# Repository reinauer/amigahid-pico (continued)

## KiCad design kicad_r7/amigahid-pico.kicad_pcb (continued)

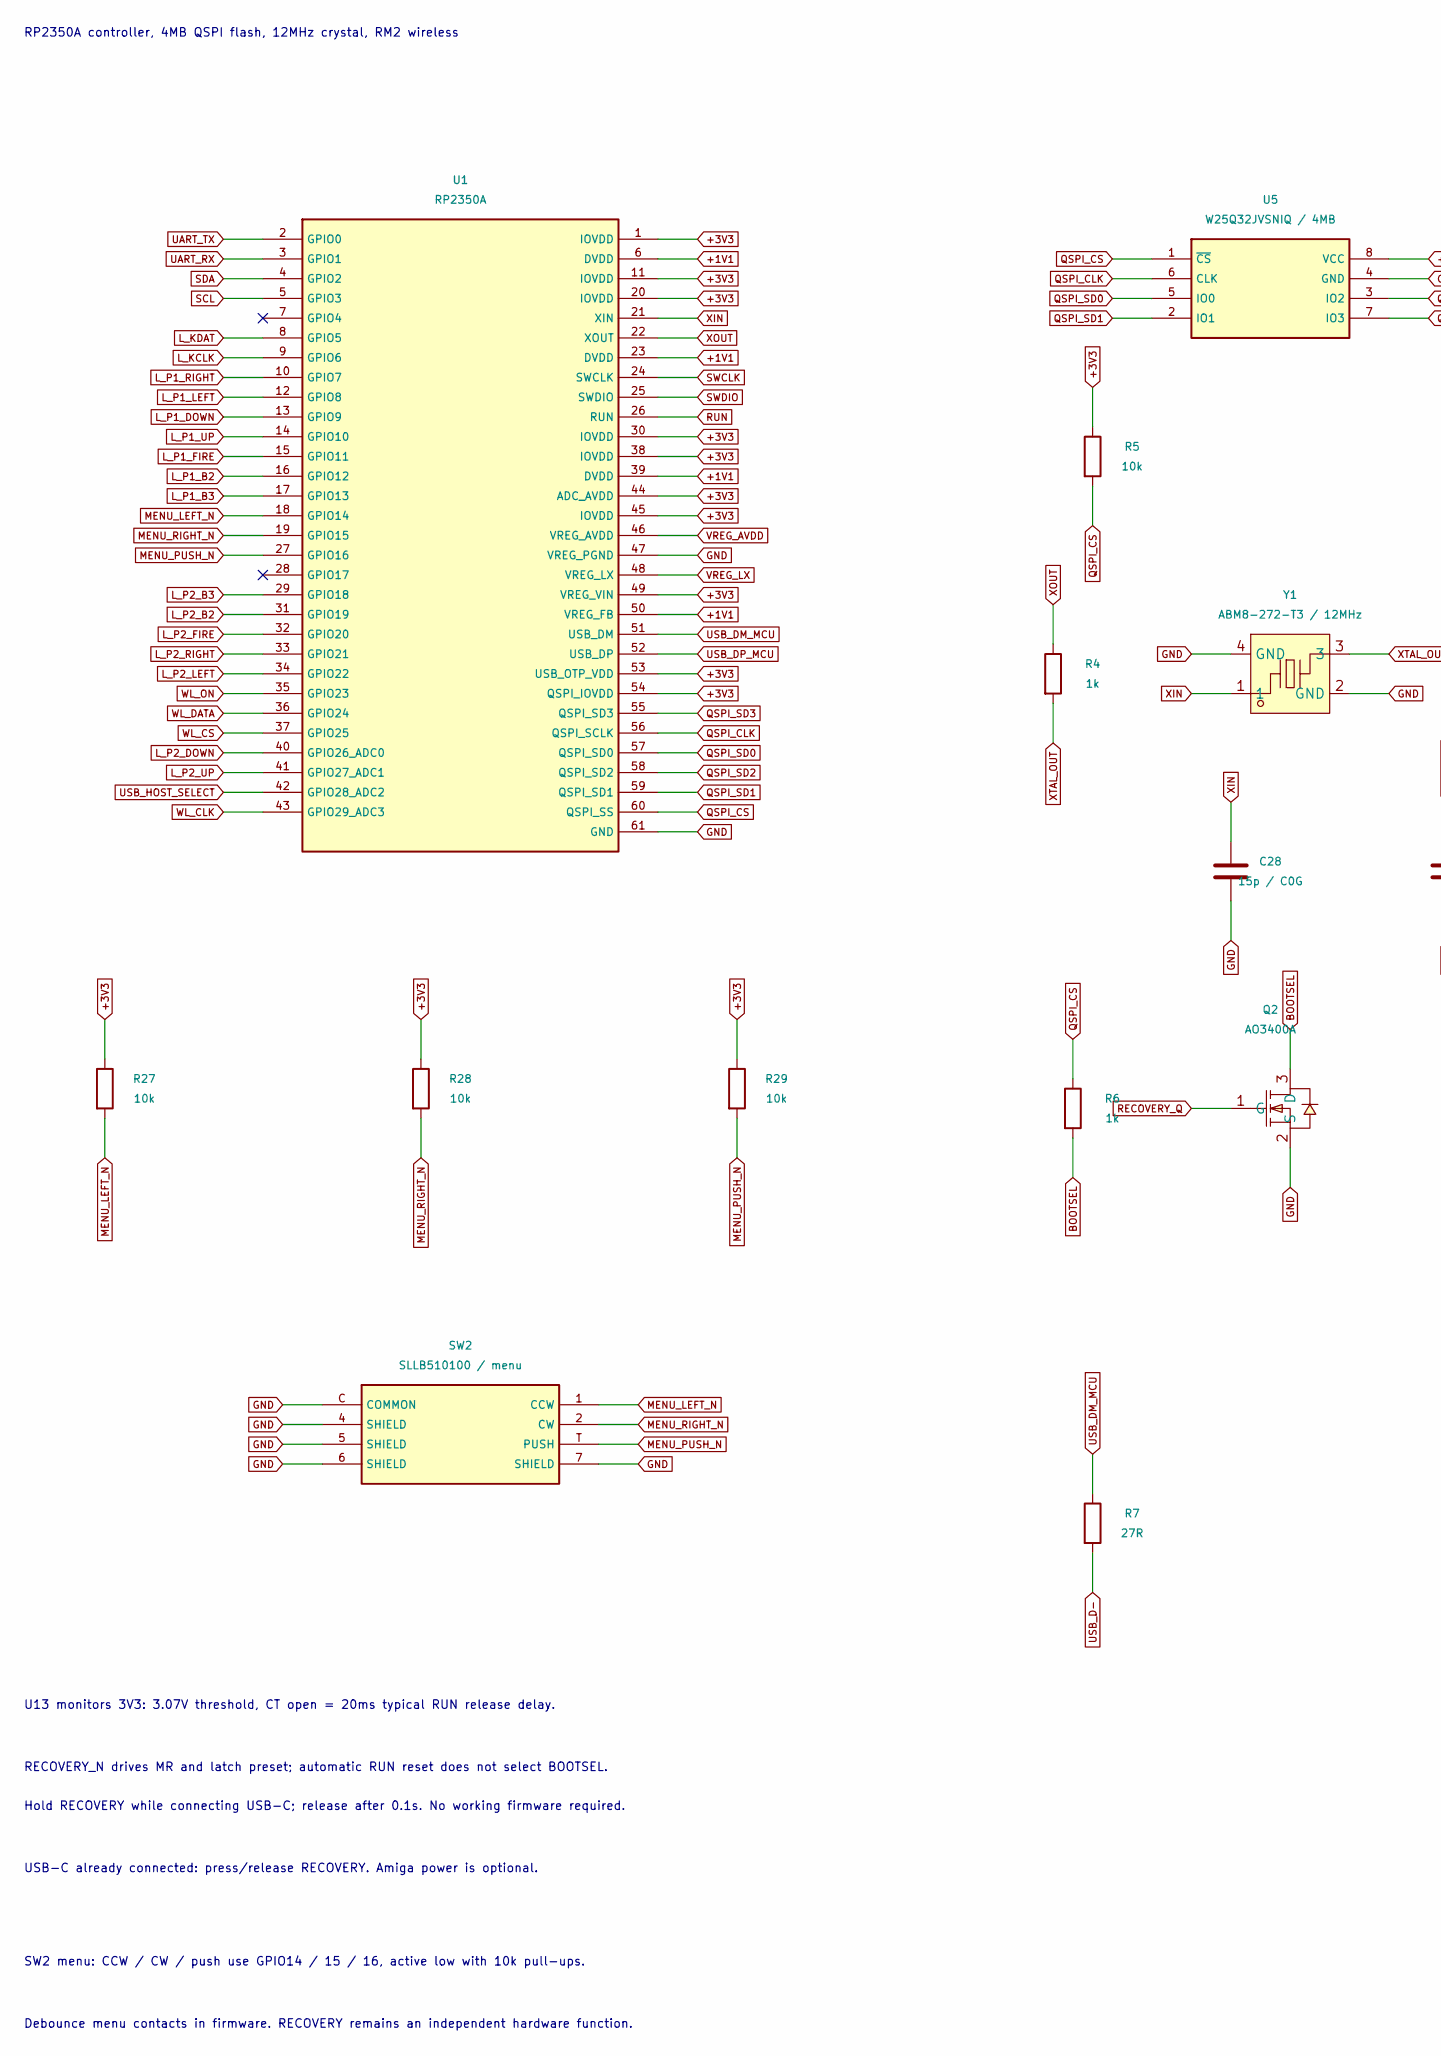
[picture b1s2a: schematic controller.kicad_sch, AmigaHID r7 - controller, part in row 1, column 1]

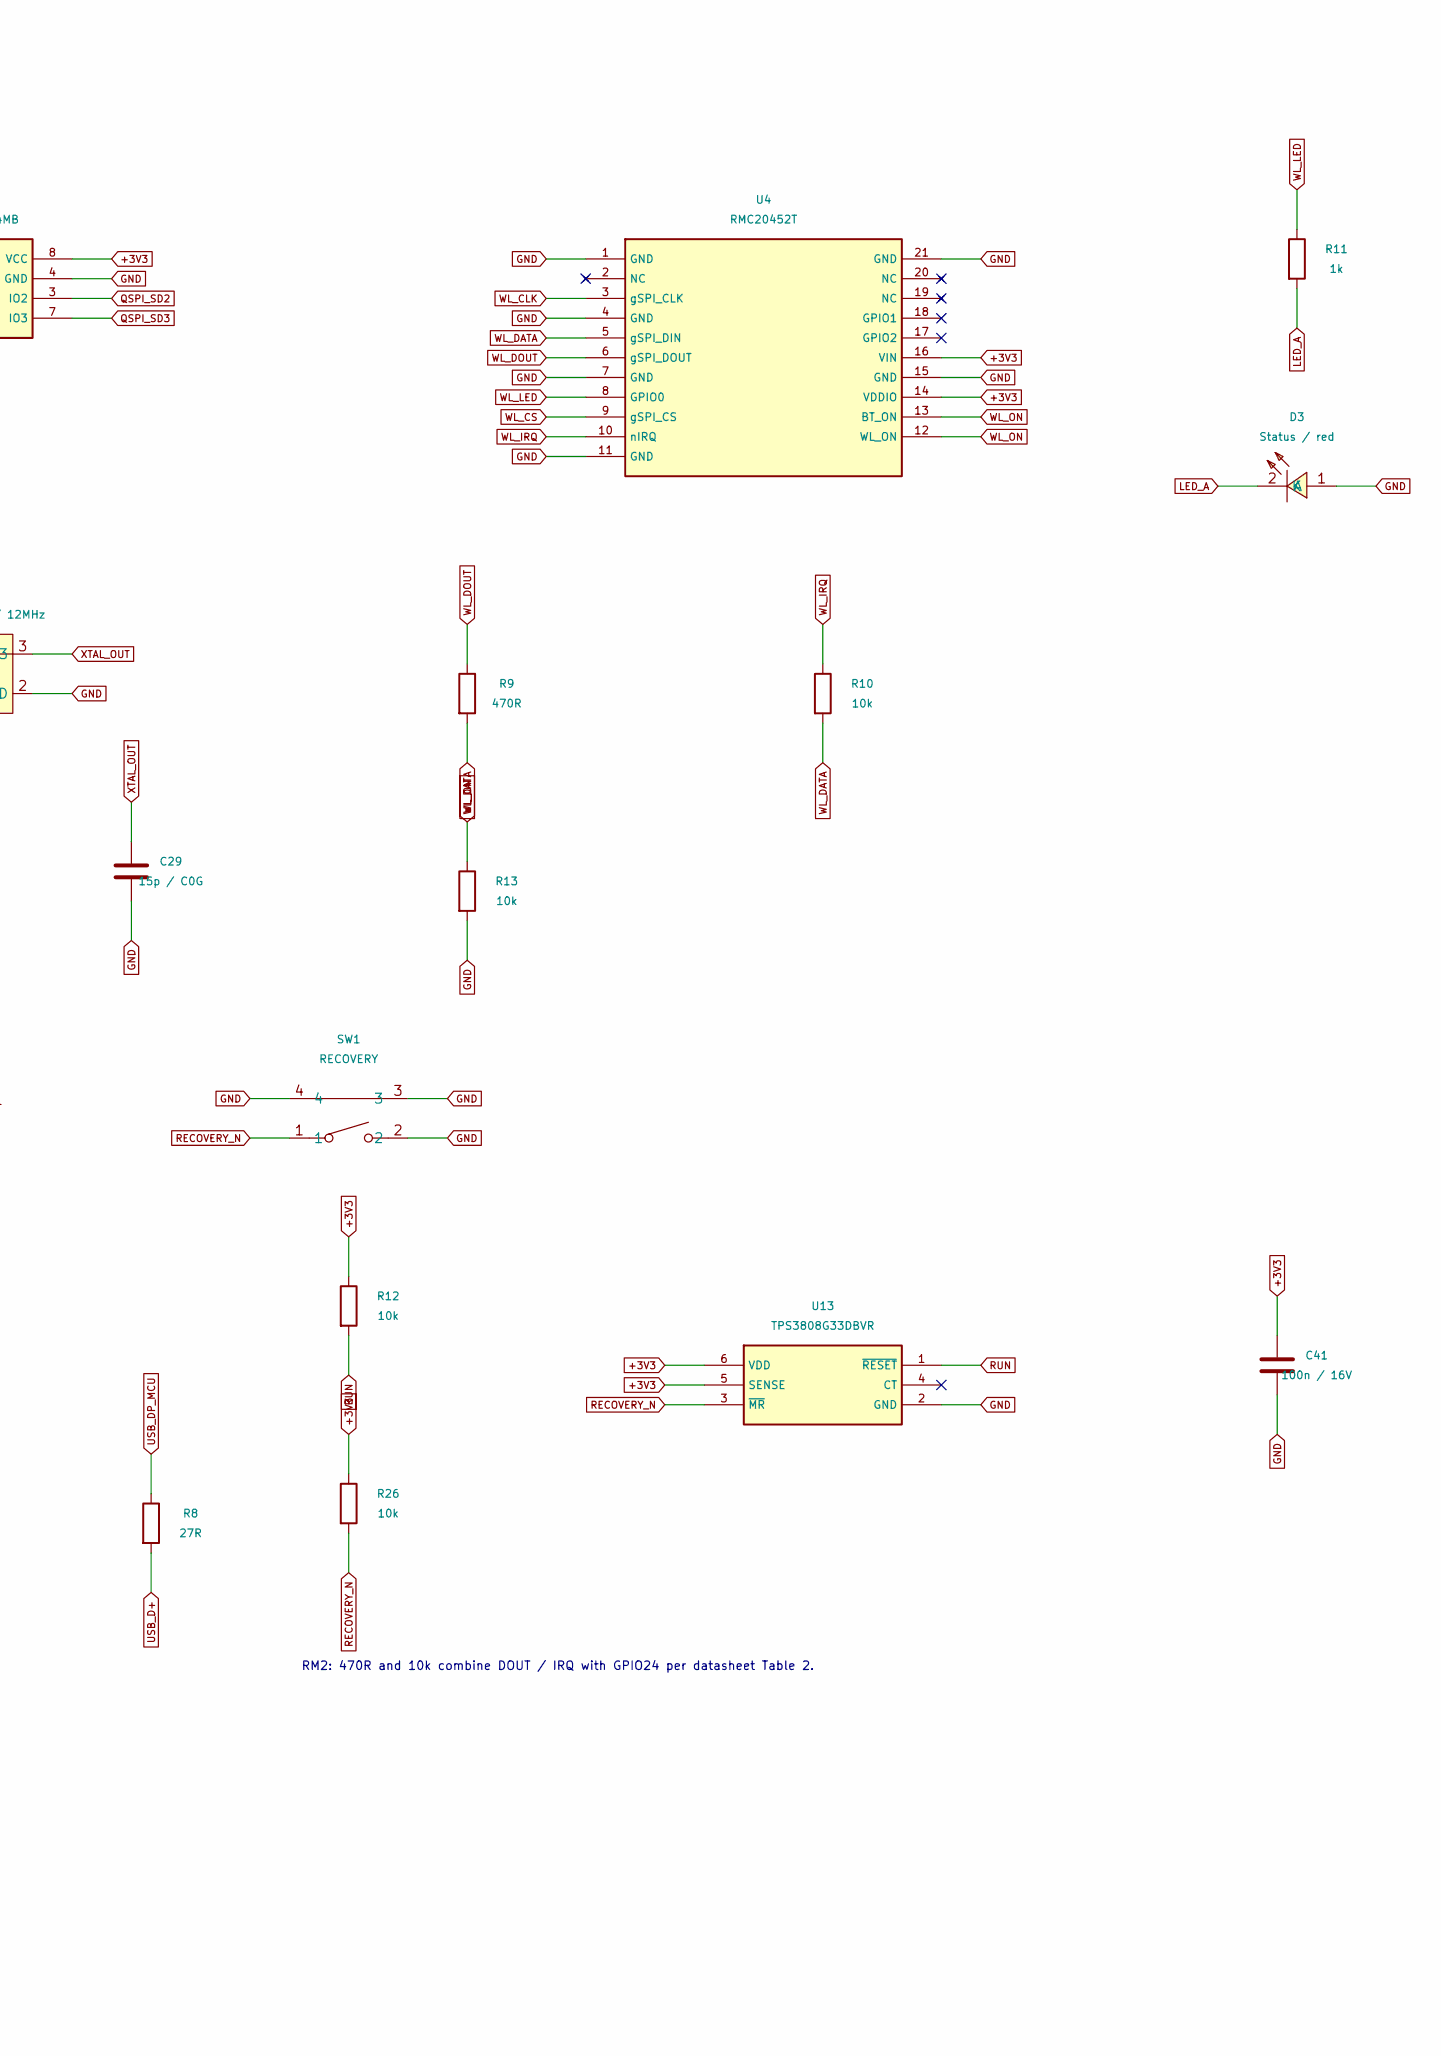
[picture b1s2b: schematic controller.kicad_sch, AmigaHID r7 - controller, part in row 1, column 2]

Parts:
C28, C29: 15p / C0G; C0402; MPN CL05C150JB5NNNC; LCSC Part # C86285
C41: 100n / 16V; C0402; MPN CL05B104KO5NNNC; LCSC Part # C1525
D3: Status / red; LED-SMD_L1.6-W0.8-R-RD; MPN KT-0603R; LCSC Part # C2286
Q2: AO3400A; SOT-23-3_L2.9-W1.3-P1.90-LS2.4-BR; MPN AO3400A; LCSC Part # C20917
R4, R6, R11: 1k; R0402; MPN 0402WGF1001TCE; LCSC Part # C11702
R5, R10, R12, R13, R26, R27, R28, R29: 10k; R0402; MPN 0402WGF1002TCE; LCSC Part # C25744
R7, R8: 27R; R0402; MPN 0402WGF270JTCE; LCSC Part # C25100
R9: 470R; R0402; MPN 0402WGF4700TCE; LCSC Part # C25117
SW1: RECOVERY; SW-SMD_2P-TS24CA; MPN TS24CA; LCSC Part # C393942
SW2: SLLB510100 / menu; SLLB510100; MPN SLLB510100; LCSC Part # C125039
U1: RP2350A; QFN-60_L7.0-W7.0-P0.40-TL-EP3.4; MPN RP2350A; LCSC Part # C42411118
U4: RMC20452T; WIRELM-SMD_RMC20452T; MPN RMC20452T; LCSC Part # C49451547
U5: W25Q32JVSNIQ / 4MB; SOP-8_L4.9-W3.9-P1.27-LS6.0-BL; MPN W25Q32JVSNIQ; LCSC Part # C5355146
U13: TPS3808G33DBVR; SOT-23-6; MPN TPS3808G33DBVR; LCSC Part # C43698
Y1: ABM8-272-T3 / 12MHz; CRYSTAL-SMD_4P-L3.2-W2.5-BL; MPN ABM8-272-T3; LCSC Part # C20625731

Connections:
+1V1: U1.6 (DVDD), U1.23 (DVDD), U1.39 (DVDD), U1.50 (VREG_FB); also elsewhere on the board
+3V3: C41.1, R5.1, R12.1, R26.1, R27.1, R28.1, R29.1, U1.1 (IOVDD), U1.11 (IOVDD), U1.20 (IOVDD), U1.30 (IOVDD), U1.38 (IOVDD), U1.44 (ADC_AVDD), U1.45 (IOVDD), U1.49 (VREG_VIN), U1.53 (USB_OTP_VDD), U1.54 (QSPI_IOVDD), U4.14 (VDDIO), U4.16 (VIN), U5.8 (VCC), U13.5 (SENSE), U13.6 (VDD); also elsewhere on the board
BOOTSEL: Q2.3 (D), R6.2
GND: C28.2, C29.2, C41.2, D3.1 (A), Q2.2 (S), R13.2, SW1.2, SW1.3, SW1.4, SW2.4 (SHIELD), SW2.5 (SHIELD), SW2.6 (SHIELD), SW2.7 (SHIELD), SW2.C (COMMON), U1.47 (VREG_PGND), U1.61 (GND), U4.1 (GND), U4.4 (GND), U4.7 (GND), U4.11 (GND), U4.15 (GND), U4.21 (GND), U5.4 (GND), U13.2 (GND), Y1.2 (GND), Y1.4 (GND); also elsewhere on the board
LED_A: D3.2 (K), R11.2
L_KCLK: U1.9 (GPIO6); also elsewhere on the board
L_KDAT: U1.8 (GPIO5); also elsewhere on the board
L_P1_B2: U1.16 (GPIO12); also elsewhere on the board
L_P1_B3: U1.17 (GPIO13); also elsewhere on the board
L_P1_DOWN: U1.13 (GPIO9); also elsewhere on the board
L_P1_FIRE: U1.15 (GPIO11); also elsewhere on the board
L_P1_LEFT: U1.12 (GPIO8); also elsewhere on the board
L_P1_RIGHT: U1.10 (GPIO7); also elsewhere on the board
L_P1_UP: U1.14 (GPIO10); also elsewhere on the board
L_P2_B2: U1.31 (GPIO19); also elsewhere on the board
L_P2_B3: U1.29 (GPIO18); also elsewhere on the board
L_P2_DOWN: U1.40 (GPIO26_ADC0); also elsewhere on the board
L_P2_FIRE: U1.32 (GPIO20); also elsewhere on the board
L_P2_LEFT: U1.34 (GPIO22); also elsewhere on the board
L_P2_RIGHT: U1.33 (GPIO21); also elsewhere on the board
L_P2_UP: U1.41 (GPIO27_ADC1); also elsewhere on the board
MENU_LEFT_N: R27.2, SW2.1 (CCW), U1.18 (GPIO14)
MENU_PUSH_N: R29.2, SW2.T (PUSH), U1.27 (GPIO16)
MENU_RIGHT_N: R28.2, SW2.2 (CW), U1.19 (GPIO15)
QSPI_CLK: U1.56 (QSPI_SCLK), U5.6 (CLK)
QSPI_CS: R5.2, R6.1, U1.60 (QSPI_SS), U5.1 (~CS)
QSPI_SD0: U1.57 (QSPI_SD0), U5.5 (IO0)
QSPI_SD1: U1.59 (QSPI_SD1), U5.2 (IO1)
QSPI_SD2: U1.58 (QSPI_SD2), U5.3 (IO2)
QSPI_SD3: U1.55 (QSPI_SD3), U5.7 (IO3)
RECOVERY_N: R26.2, SW1.1, U13.3 (~MR); also elsewhere on the board
RECOVERY_Q: Q2.1 (G); also elsewhere on the board
RUN: R12.2, U1.26 (RUN), U13.1 (~RESET); also elsewhere on the board
SCL: U1.5 (GPIO3); also elsewhere on the board
SDA: U1.4 (GPIO2); also elsewhere on the board
SWCLK: U1.24 (SWCLK); also elsewhere on the board
SWDIO: U1.25 (SWDIO); also elsewhere on the board
UART_RX: U1.3 (GPIO1); also elsewhere on the board
UART_TX: U1.2 (GPIO0); also elsewhere on the board
USB_D+: R8.2; also elsewhere on the board
USB_D-: R7.2; also elsewhere on the board
USB_DM_MCU: R7.1, U1.51 (USB_DM)
USB_DP_MCU: R8.1, U1.52 (USB_DP)
USB_HOST_SELECT: U1.42 (GPIO28_ADC2); also elsewhere on the board
VREG_AVDD: U1.46 (VREG_AVDD); also elsewhere on the board
VREG_LX: U1.48 (VREG_LX); also elsewhere on the board
WL_CLK: U1.43 (GPIO29_ADC3), U4.3 (gSPI_CLK)
WL_CS: U1.37 (GPIO25), U4.9 (gSPI_CS)
WL_DATA: R9.2, R10.2, U1.36 (GPIO24), U4.5 (gSPI_DIN)
WL_DOUT: R9.1, U4.6 (gSPI_DOUT)
WL_IRQ: R10.1, U4.10 (nIRQ)
WL_LED: R11.1, U4.8 (GPIO0)
WL_ON: R13.1, U1.35 (GPIO23), U4.12 (WL_ON), U4.13 (BT_ON)
XIN: C28.1, U1.21 (XIN), Y1.1
XOUT: R4.1, U1.22 (XOUT)
XTAL_OUT: C29.1, R4.2, Y1.3

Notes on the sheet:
RP2350A controller, 4MB QSPI flash, 12MHz crystal, RM2 wireless
U13 monitors 3V3: 3.07V threshold, CT open = 20ms typical RUN release delay.
RECOVERY_N drives MR and latch preset; automatic RUN reset does not select BOOTSEL.
RM2: 470R and 10k combine DOUT / IRQ with GPIO24 per datasheet Table 2.
Hold RECOVERY while connecting USB-C; release after 0.1s. No working firmware required.
USB-C already connected: press/release RECOVERY. Amiga power is optional.
SW2 menu: CCW / CW / push use GPIO14 / 15 / 16, active low with 10k pull-ups.
Debounce menu contacts in firmware. RECOVERY remains an independent hardware function.

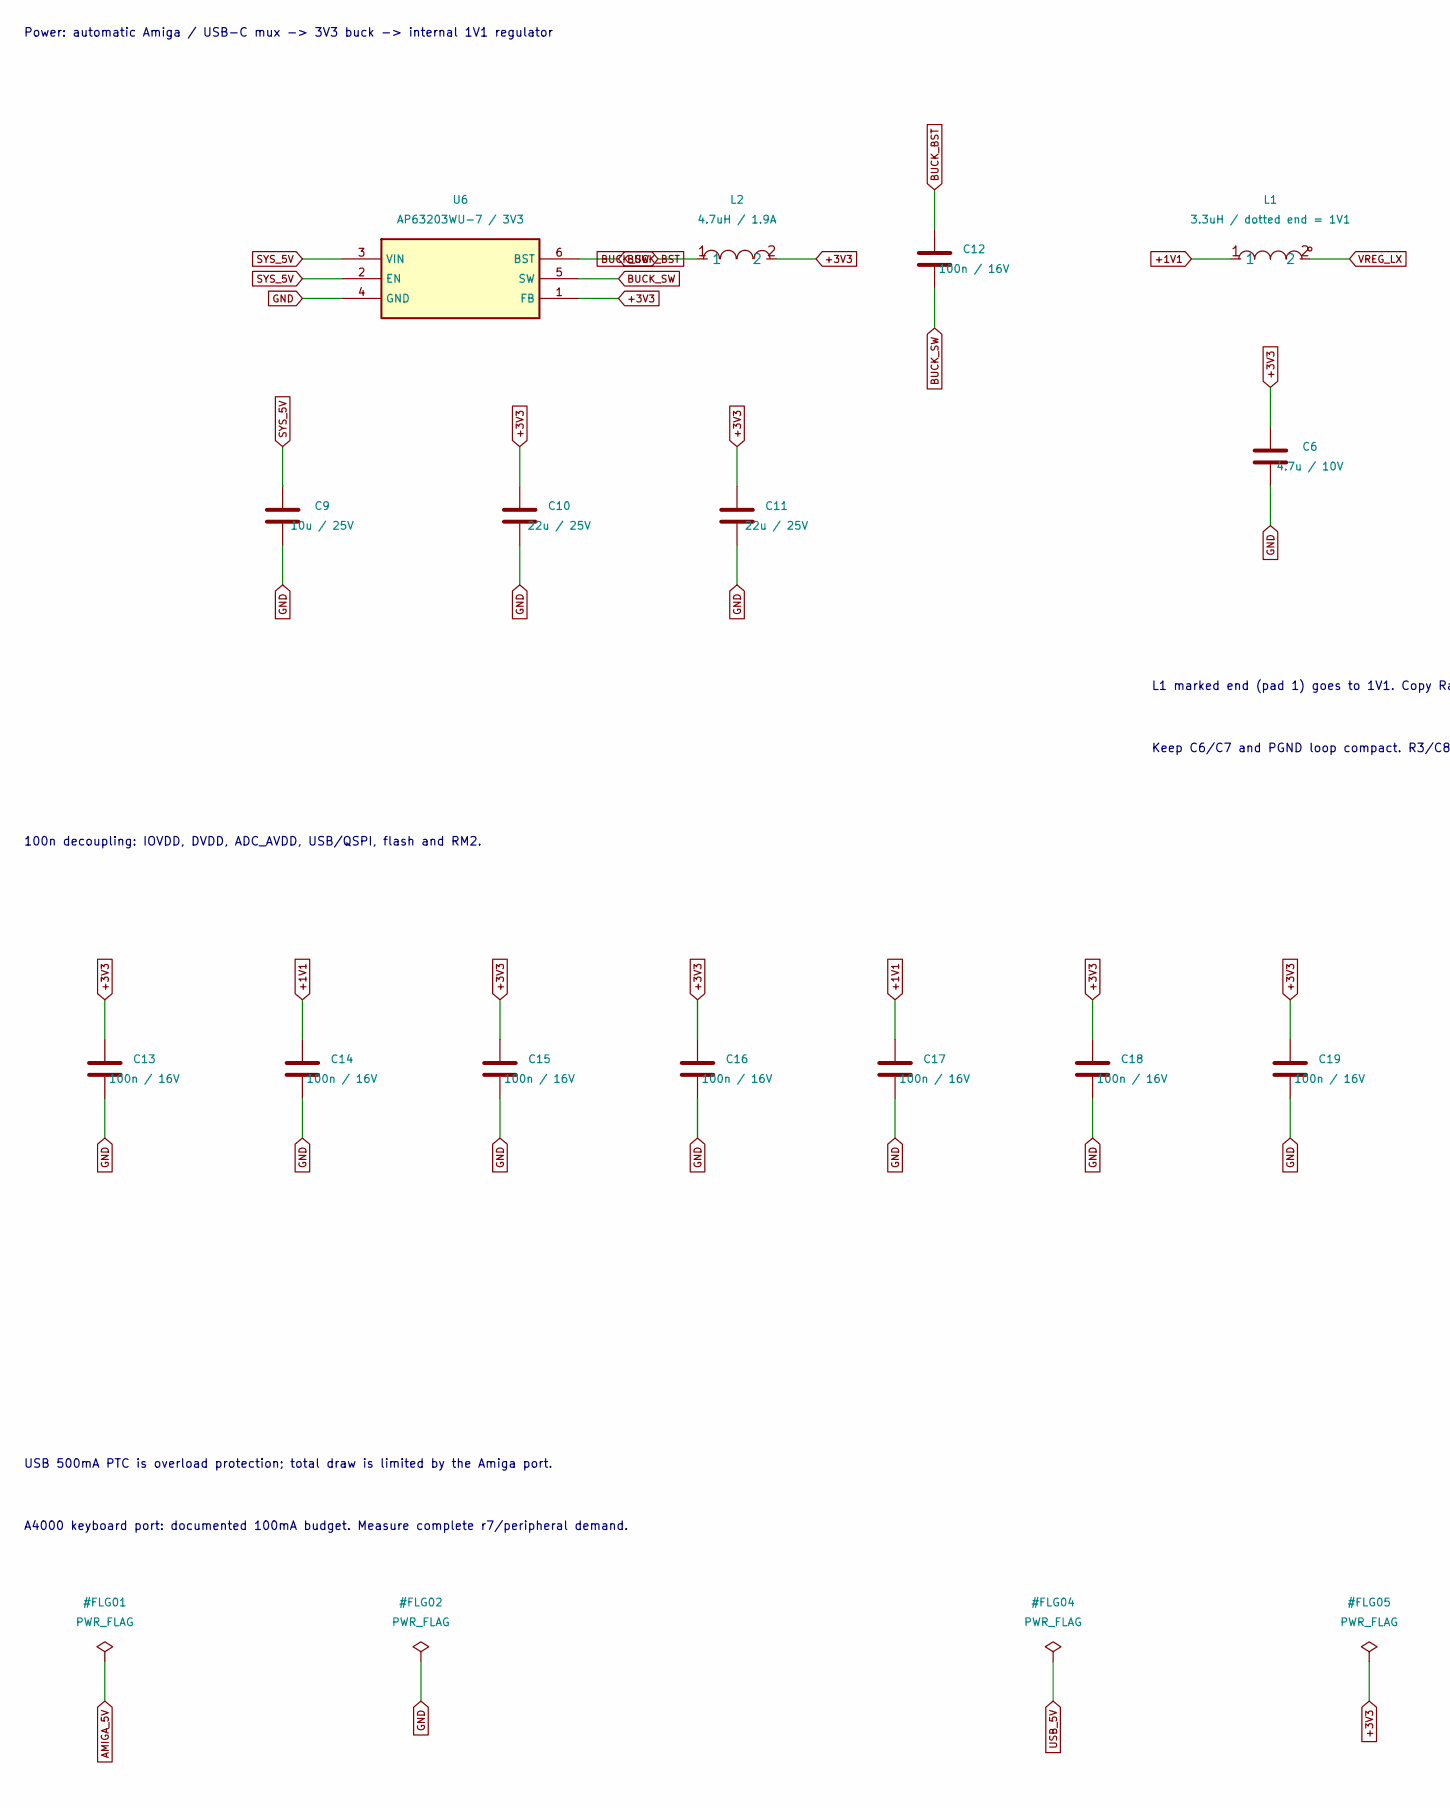
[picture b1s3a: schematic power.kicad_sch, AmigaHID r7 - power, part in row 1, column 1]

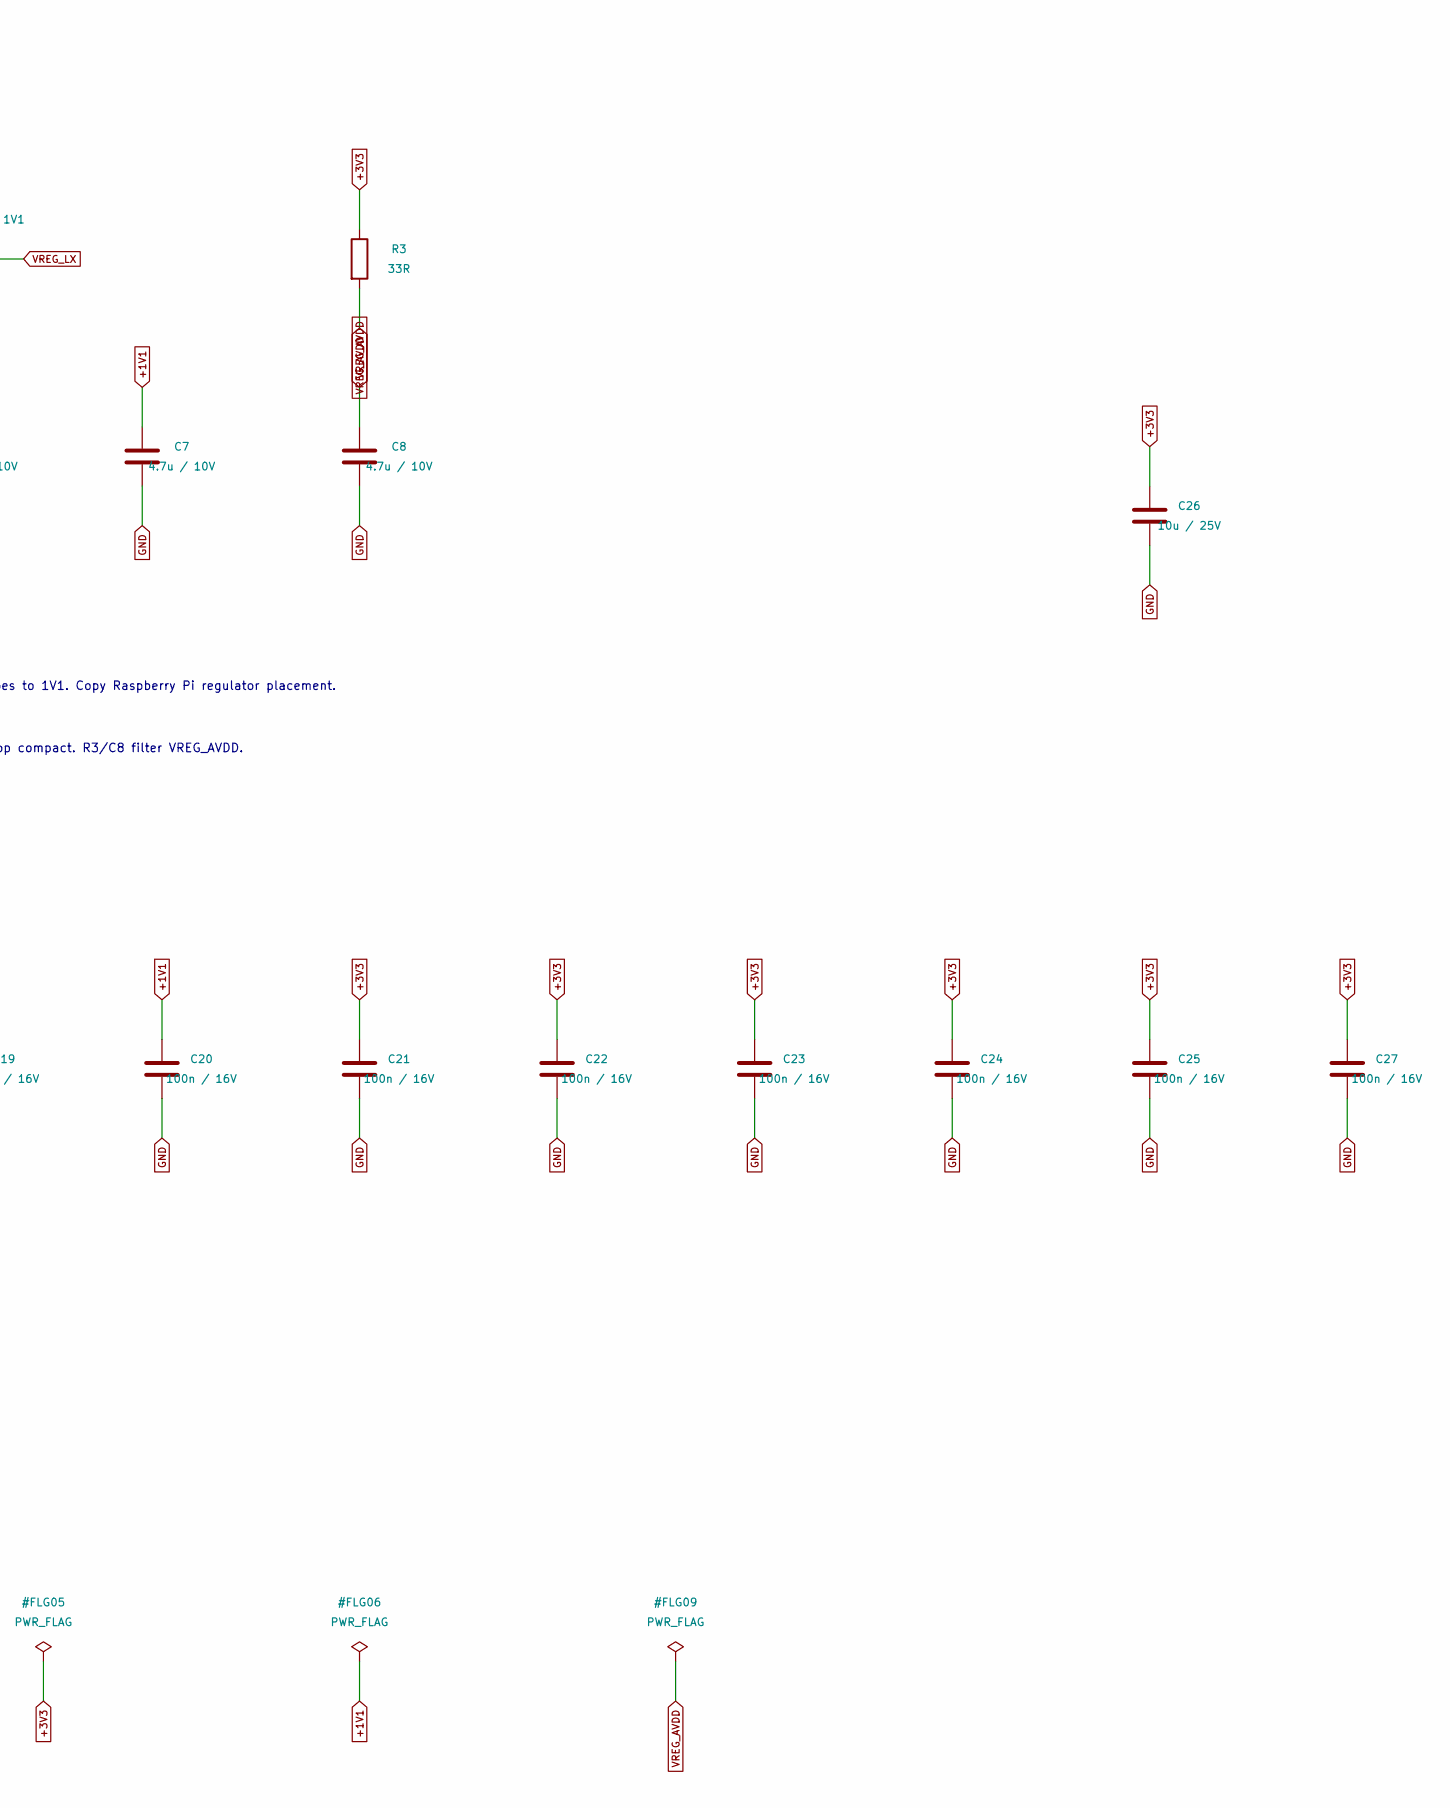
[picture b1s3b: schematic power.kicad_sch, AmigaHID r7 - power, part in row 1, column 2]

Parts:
C6, C7, C8: 4.7u / 10V; C0402; MPN CL05A475MP5NRNC; LCSC Part # C23733
C9, C26: 10u / 25V; C0805; MPN CL21A106KAYNNNE; LCSC Part # C15850
C10, C11: 22u / 25V; C0805; MPN CL21A226MAQNNNE; LCSC Part # C45783
C12, C13, C14, C15, C16, C17, C18, C19, C20, C21, C22, C23, C24, C25, C27: 100n / 16V; C0402; MPN CL05B104KO5NNNC; LCSC Part # C1525
L1: 3.3uH / dotted end = 1V1; IND-SMD_L2.0-W1.6_AOTA-B201610S3R3-101-T; MPN AOTA-B201610S3R3-101-T; LCSC Part # C42411119
L2: 4.7uH / 1.9A; IND-SMD_L4.0-W4.0_SRN4018TA; MPN SRN4018-4R7M; LCSC Part # C780206
R3: 33R; R0402; MPN 0402WGF330JTCE; LCSC Part # C25105
U6: AP63203WU-7 / 3V3; TSOT-26_L2.9-W1.6-P0.95-LS2.8-BL; MPN AP63203WU-7; LCSC Part # C780769

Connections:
+1V1: C7.1, C14.1, C17.1, C20.1, L1.1; also elsewhere on the board
+3V3: C6.1, C10.1, C11.1, C13.1, C15.1, C16.1, C18.1, C19.1, C21.1, C22.1, C23.1, C24.1, C25.1, C26.1, C27.1, L2.2, R3.1, U6.1 (FB); also elsewhere on the board
BUCK_BST: C12.1, U6.6 (BST)
BUCK_SW: C12.2, L2.1, U6.5 (SW)
GND: C6.2, C7.2, C8.2, C9.2, C10.2, C11.2, C13.2, C14.2, C15.2, C16.2, C17.2, C18.2, C19.2, C20.2, C21.2, C22.2, C23.2, C24.2, C25.2, C26.2, C27.2, U6.4 (GND); also elsewhere on the board
SYS_5V: C9.1, U6.2 (EN), U6.3 (VIN); also elsewhere on the board
VREG_AVDD: C8.1, R3.2; also elsewhere on the board
VREG_LX: L1.2; also elsewhere on the board

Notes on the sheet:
Power: automatic Amiga / USB-C mux -> 3V3 buck -> internal 1V1 regulator
L1 marked end (pad 1) goes to 1V1. Copy Raspberry Pi regulator placement.
100n decoupling: IOVDD, DVDD, ADC_AVDD, USB/QSPI, flash and RM2.
Keep C6/C7 and PGND loop compact. R3/C8 filter VREG_AVDD.
USB 500mA PTC is overload protection; total draw is limited by the Amiga port.
A4000 keyboard port: documented 100mA budget. Measure complete r7/peripheral demand.

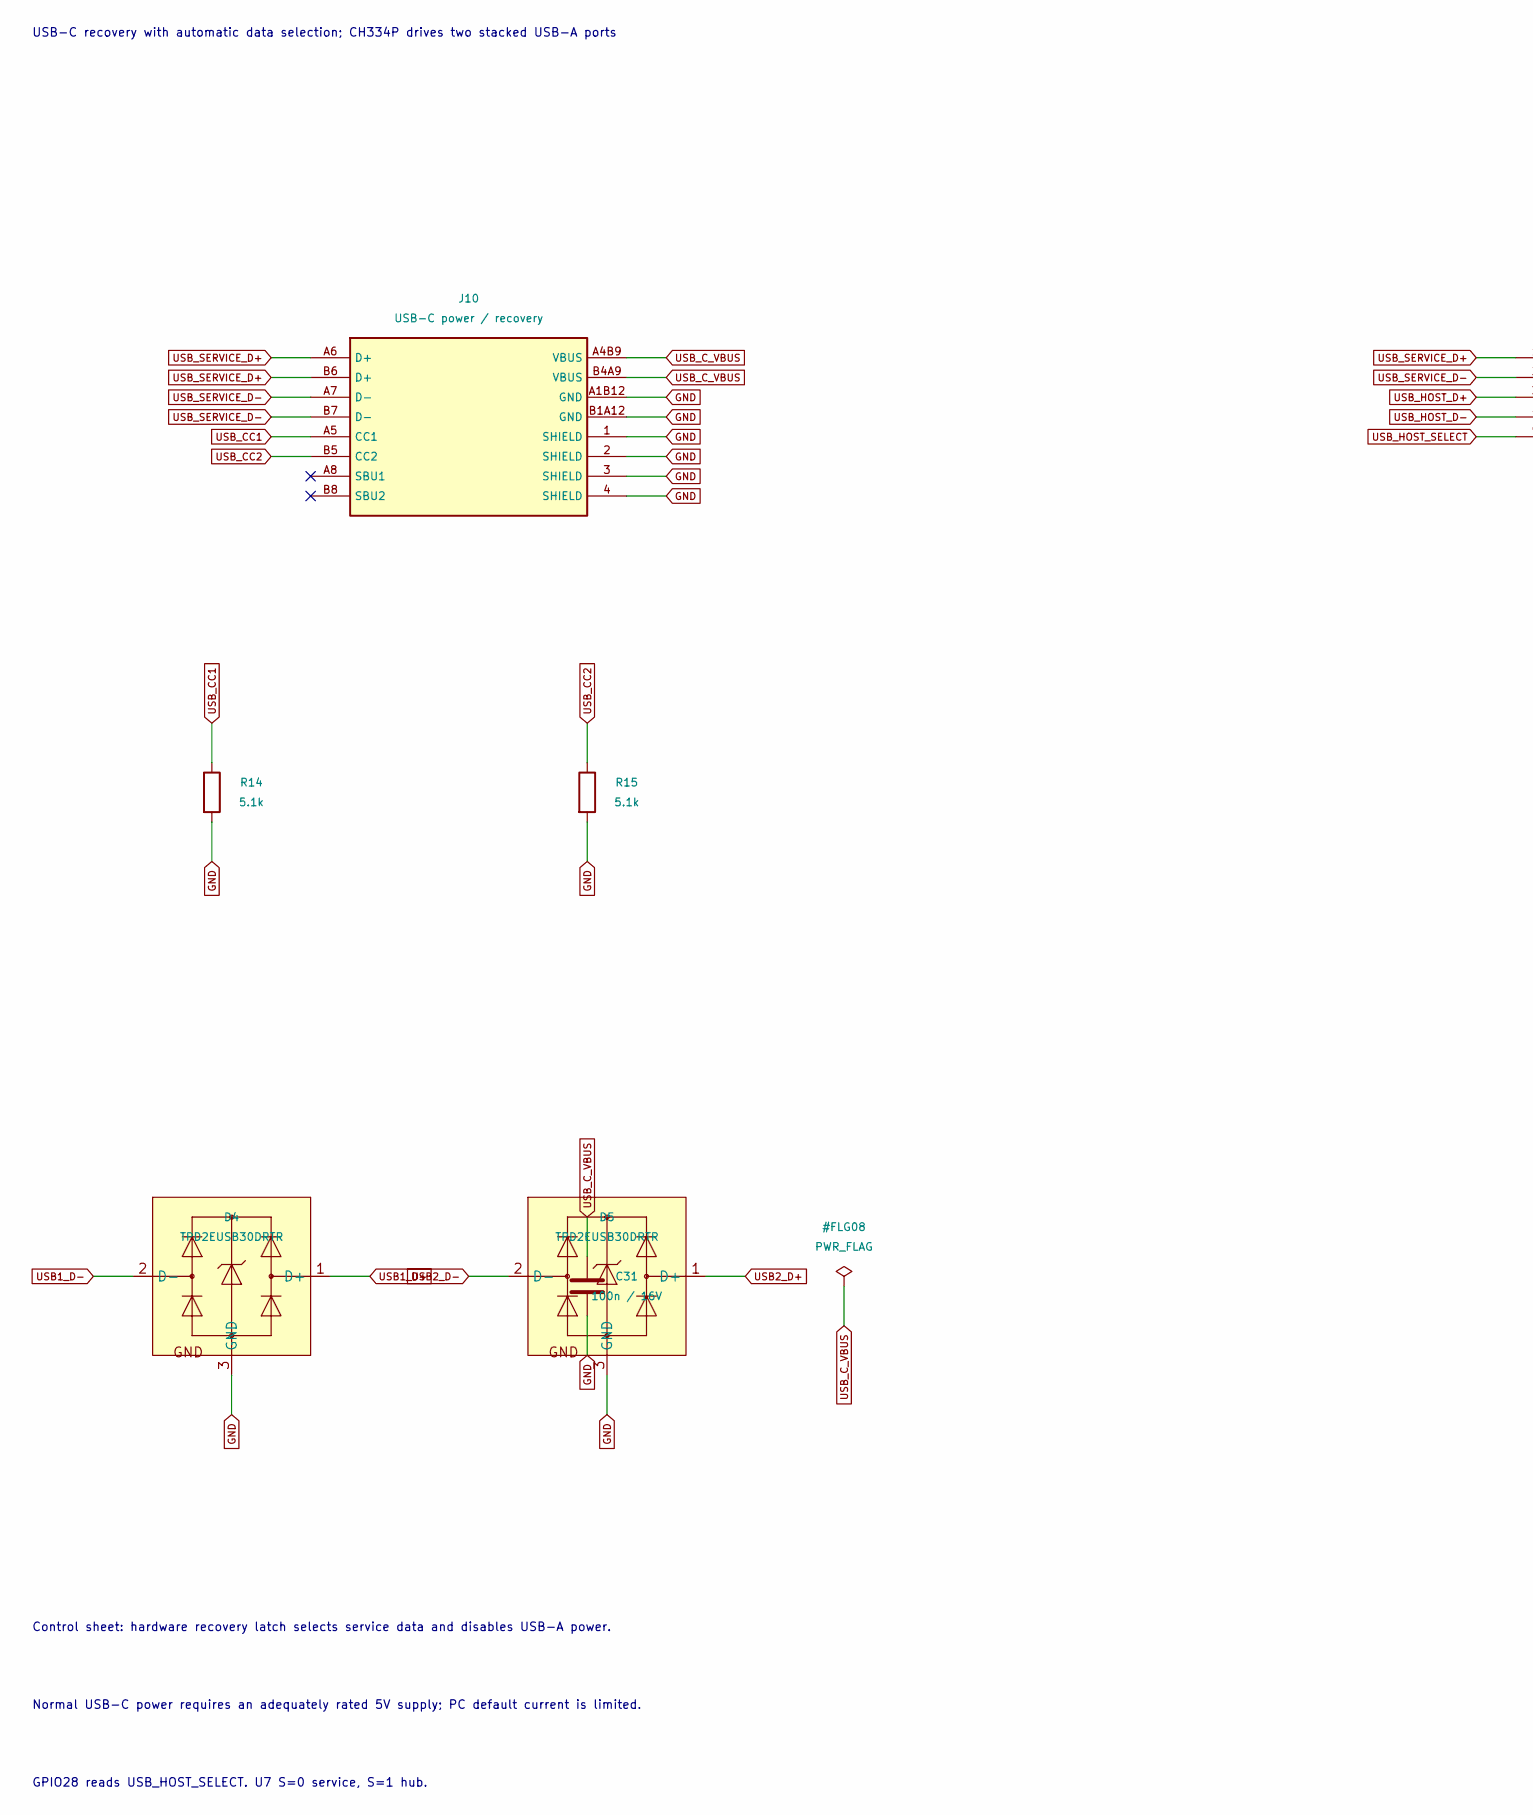
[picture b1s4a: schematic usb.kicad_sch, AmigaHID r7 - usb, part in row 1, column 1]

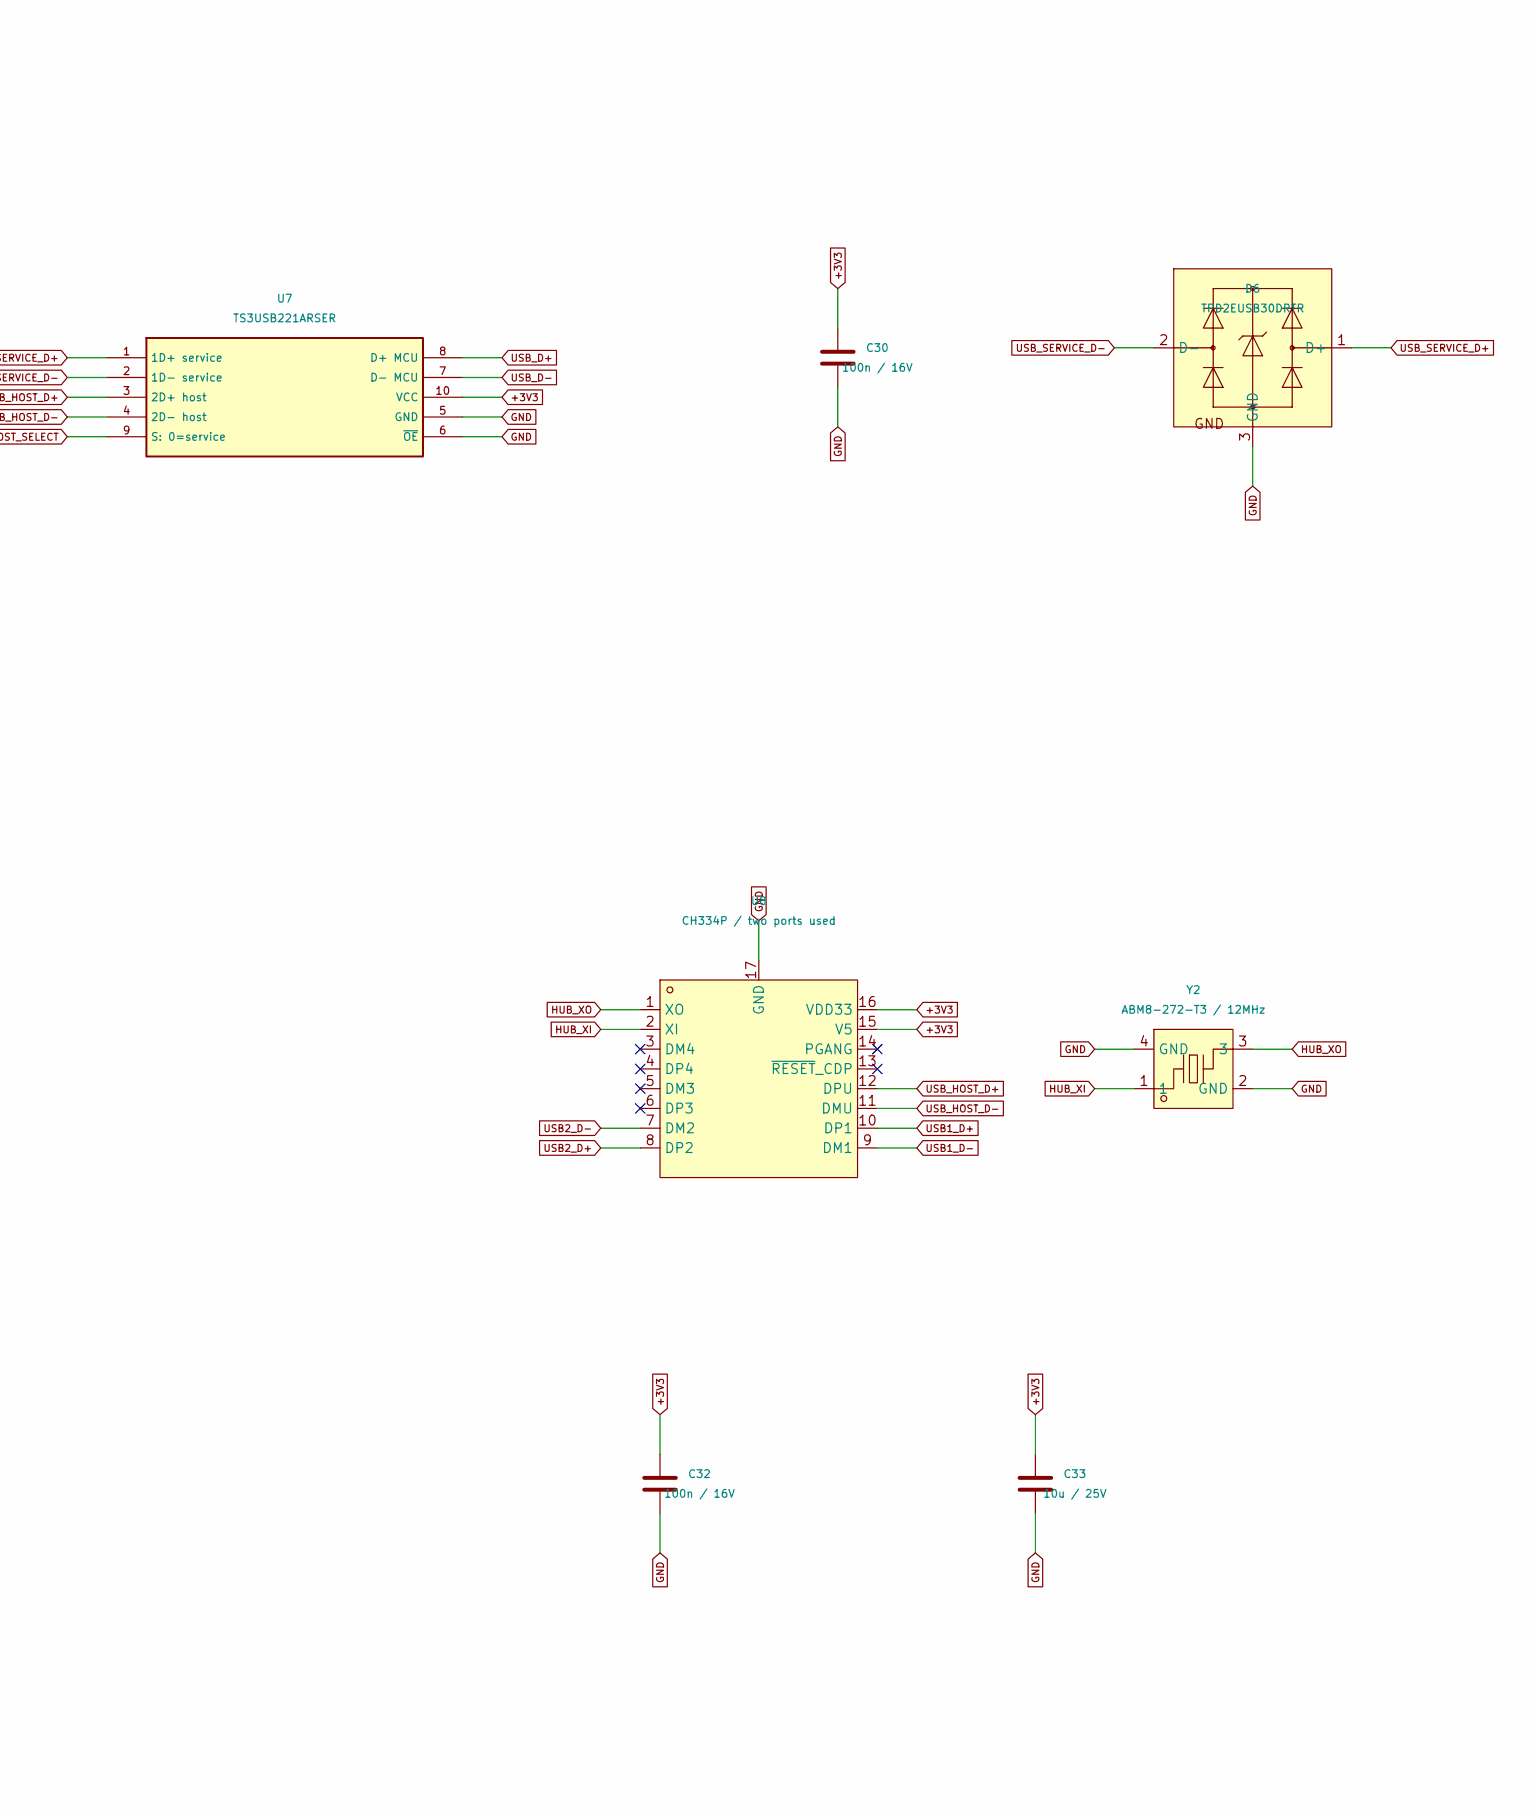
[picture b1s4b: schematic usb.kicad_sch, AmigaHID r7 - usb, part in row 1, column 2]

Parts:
C30, C31, C32: 100n / 16V; C0402; MPN CL05B104KO5NNNC; LCSC Part # C1525
C33: 10u / 25V; C0805; MPN CL21A106KAYNNNE; LCSC Part # C15850
D4, D5, D6: TPD2EUSB30DRTR; SOT-9X3-3_L1.0-W0.8-P0.35-LS1.0-BR; MPN TPD2EUSB30DRTR; LCSC Part # C97502
J10: USB-C power / recovery; USB-C_SMD-TYPE-C-31-M-12_1; MPN TYPE-C-31-M-12; LCSC Part # C165948
R14, R15: 5.1k; R0402; MPN 0402WGF5101TCE; LCSC Part # C25905
U7: TS3USB221ARSER; UQFN-10_L2.0-W1.5-P0.50-BL; MPN TS3USB221ARSER; LCSC Part # C128396
U8: CH334P / two ports used; QFN-16_L3.0-W3.0-P0.50-BL-EP1.7; MPN CH334P; LCSC Part # C5373042
Y2: ABM8-272-T3 / 12MHz; CRYSTAL-SMD_4P-L3.2-W2.5-BL; MPN ABM8-272-T3; LCSC Part # C20625731

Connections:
+3V3: C30.1, C32.1, C33.1, U7.10 (VCC), U8.15 (V5), U8.16 (VDD33); also elsewhere on the board
GND: C30.2, C31.2, C32.2, C33.2, D4.3 (GND), D5.3 (GND), D6.3 (GND), J10.1 (SHIELD), J10.2 (SHIELD), J10.3 (SHIELD), J10.4 (SHIELD), J10.A1B12 (GND), J10.B1A12 (GND), R14.2, R15.2, U7.5 (GND), U7.6 (~OE), U8.17 (GND), Y2.2 (GND), Y2.4 (GND); also elsewhere on the board
HUB_XI: U8.2 (XI), Y2.1
HUB_XO: U8.1 (XO), Y2.3
USB1_D+: D4.1 (D+), U8.10 (DP1); also elsewhere on the board
USB1_D-: D4.2 (D-), U8.9 (DM1); also elsewhere on the board
USB2_D+: D5.1 (D+), U8.8 (DP2); also elsewhere on the board
USB2_D-: D5.2 (D-), U8.7 (DM2); also elsewhere on the board
USB_CC1: J10.A5 (CC1), R14.1
USB_CC2: J10.B5 (CC2), R15.1
USB_C_VBUS: C31.1, J10.A4B9 (VBUS), J10.B4A9 (VBUS); also elsewhere on the board
USB_D+: U7.8 (D+ MCU); also elsewhere on the board
USB_D-: U7.7 (D- MCU); also elsewhere on the board
USB_HOST_D+: U7.3 (2D+ host), U8.12 (DPU)
USB_HOST_D-: U7.4 (2D- host), U8.11 (DMU)
USB_HOST_SELECT: U7.9 (S: 0=service); also elsewhere on the board
USB_SERVICE_D+: D6.1 (D+), J10.A6 (D+), J10.B6 (D+), U7.1 (1D+ service)
USB_SERVICE_D-: D6.2 (D-), J10.A7 (D-), J10.B7 (D-), U7.2 (1D- service)

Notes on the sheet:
USB-C recovery with automatic data selection; CH334P drives two stacked USB-A ports
Control sheet: hardware recovery latch selects service data and disables USB-A power.
Normal USB-C power requires an adequately rated 5V supply; PC default current is limited.
GPIO28 reads USB_HOST_SELECT. U7 S=0 service, S=1 hub.
